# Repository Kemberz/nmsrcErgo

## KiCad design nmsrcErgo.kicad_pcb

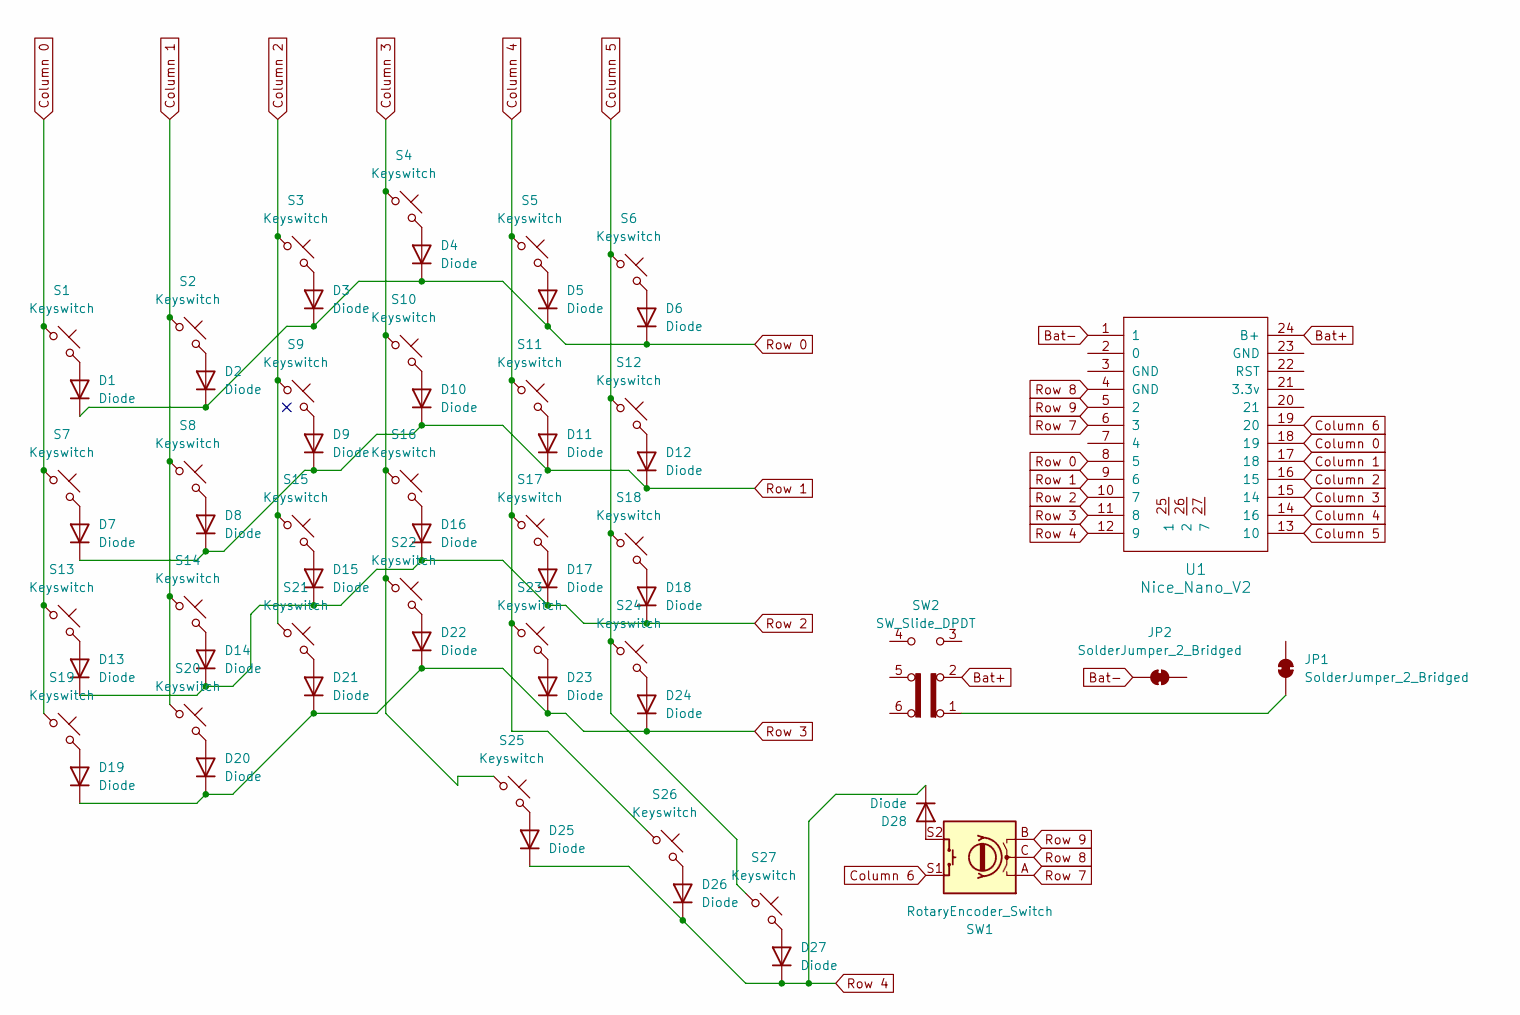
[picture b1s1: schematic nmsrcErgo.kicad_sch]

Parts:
D1, D2, D3, D4, D5, D6, D7, D8, D9, D10, D11, D12, D13, D14, D15, D16, D17, D18, D19, D20, D21, D22, D23, D24, D25, D26, D27, D28: Diode; Diode_DO-35
JP1, JP2: SolderJumper_2_Bridged; solderpadv2
S1, S2, S3, S4, S5, S6, S7, S8, S9, S10, S11, S12, S13, S14, S15, S16, S17, S18, S19, S20, S21, S22, S23, S24, S25, S26, S27: Keyswitch; Hotswap_Choc_V1
SW1: RotaryEncoder_Switch; Encoder_EC11_MX
SW2: SW_Slide_DPDT; SW_Slide-03_Wuerth-WS-SLTV_10x2.5x6.4_P2.54mm
U1: Nice_Nano_V2

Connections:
Bat+: SW2.2 (B), U1.24 (B+)
Bat-: JP2.1 (A), U1.1; also elsewhere on the board
Column 0: S1.1, S7.1, S13.1, S19.1, U1.18 (19)
Column 1: S2.1, S8.1, S14.1, S20.1, U1.17 (18)
Column 2: S3.1, S9.1, S15.1, S21.1, U1.16 (15)
Column 3: S4.1, S10.1, S16.1, S22.1, S25.1, U1.15 (14)
Column 4: S5.1, S11.1, S17.1, S23.1, S26.1, U1.14 (16)
Column 5: S6.1, S12.1, S18.1, S24.1, S27.1, U1.13 (10)
Column 6: SW1.S1, U1.19 (20)
unnamed: D1.2 (A), S1.2
unnamed: D2.2 (A), S2.2
unnamed: D3.2 (A), S3.2
unnamed: D4.2 (A), S4.2
unnamed: D5.2 (A), S5.2
unnamed: D6.2 (A), S6.2
unnamed: D7.2 (A), S7.2
unnamed: D8.2 (A), S8.2
unnamed: D9.2 (A), S9.2
unnamed: D10.2 (A), S10.2
unnamed: D11.2 (A), S11.2
unnamed: D12.2 (A), S12.2
unnamed: D13.2 (A), S13.2
unnamed: D14.2 (A), S14.2
unnamed: D15.2 (A), S15.2
unnamed: D16.2 (A), S16.2
unnamed: D17.2 (A), S17.2
unnamed: D18.2 (A), S18.2
unnamed: D19.2 (A), S19.2
unnamed: D20.2 (A), S20.2
unnamed: D21.2 (A), S21.2
unnamed: D22.2 (A), S22.2
unnamed: D23.2 (A), S23.2
unnamed: D24.2 (A), S24.2
unnamed: D25.2 (A), S25.2
unnamed: D26.2 (A), S26.2
unnamed: D27.2 (A), S27.2
unnamed: D28.2 (A), SW1.S2
unnamed 37: JP1.1 (A), SW2.1 (A); also elsewhere on the board
Row 0: D1.1 (K), D2.1 (K), D3.1 (K), D4.1 (K), D5.1 (K), D6.1 (K), U1.8 (5)
Row 1: D7.1 (K), D8.1 (K), D9.1 (K), D10.1 (K), D11.1 (K), D12.1 (K), U1.9 (6)
Row 2: D13.1 (K), D14.1 (K), D15.1 (K), D16.1 (K), D17.1 (K), D18.1 (K), U1.10 (7)
Row 3: D19.1 (K), D20.1 (K), D21.1 (K), D22.1 (K), D23.1 (K), D24.1 (K), U1.11 (8)
Row 4: D25.1 (K), D26.1 (K), D27.1 (K), D28.1 (K), U1.12 (9)
Row 7: SW1.A, U1.6 (3)
Row 8: SW1.C, U1.4 (GND)
Row 9: SW1.B, U1.5 (2)

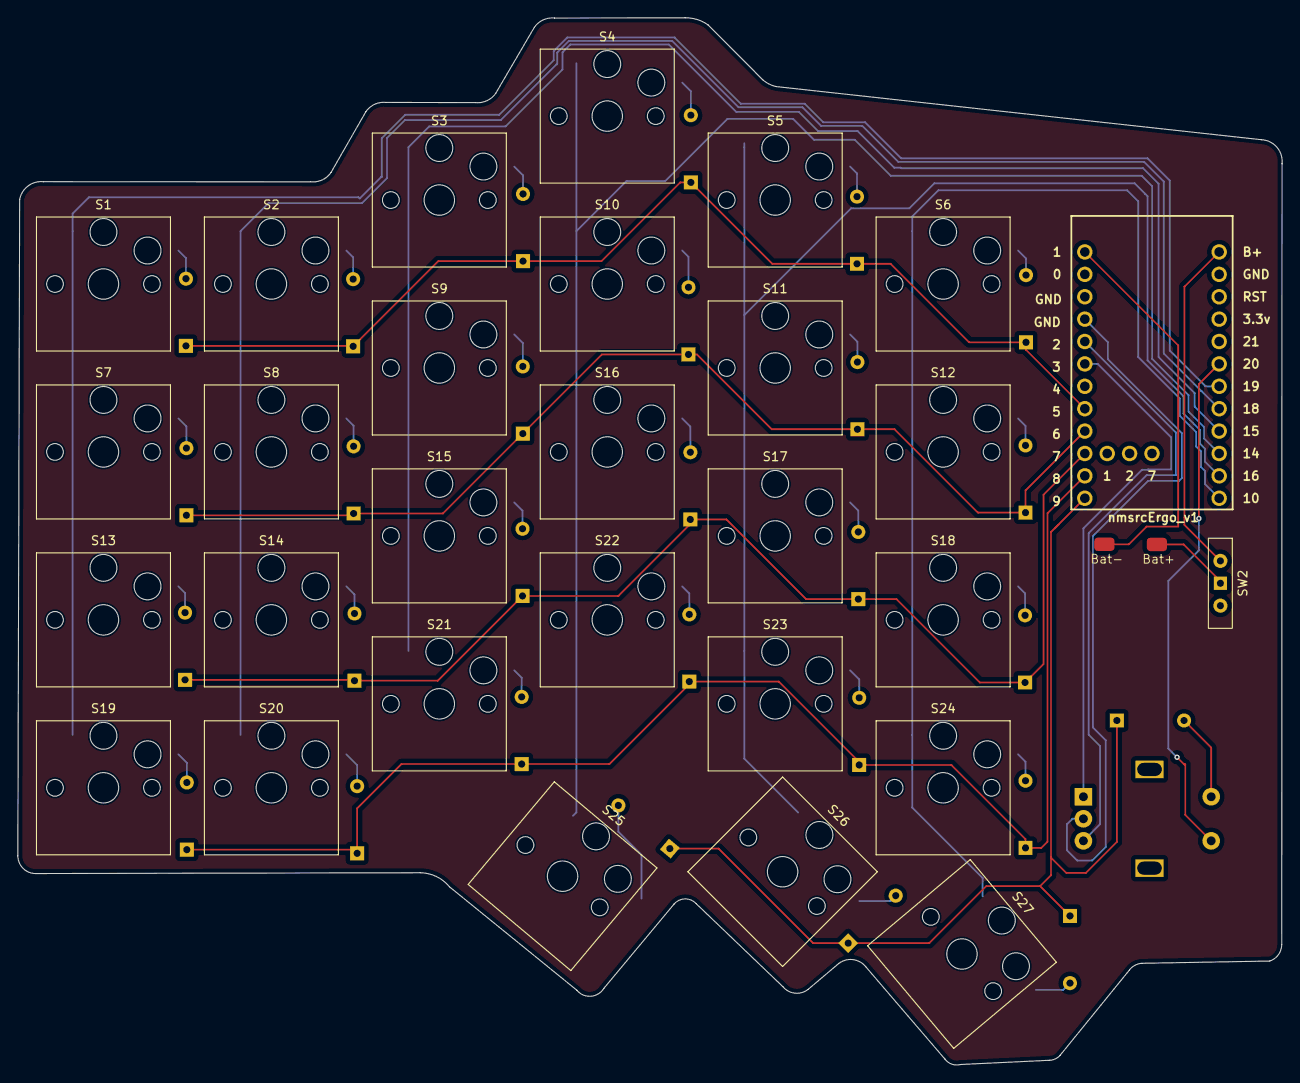
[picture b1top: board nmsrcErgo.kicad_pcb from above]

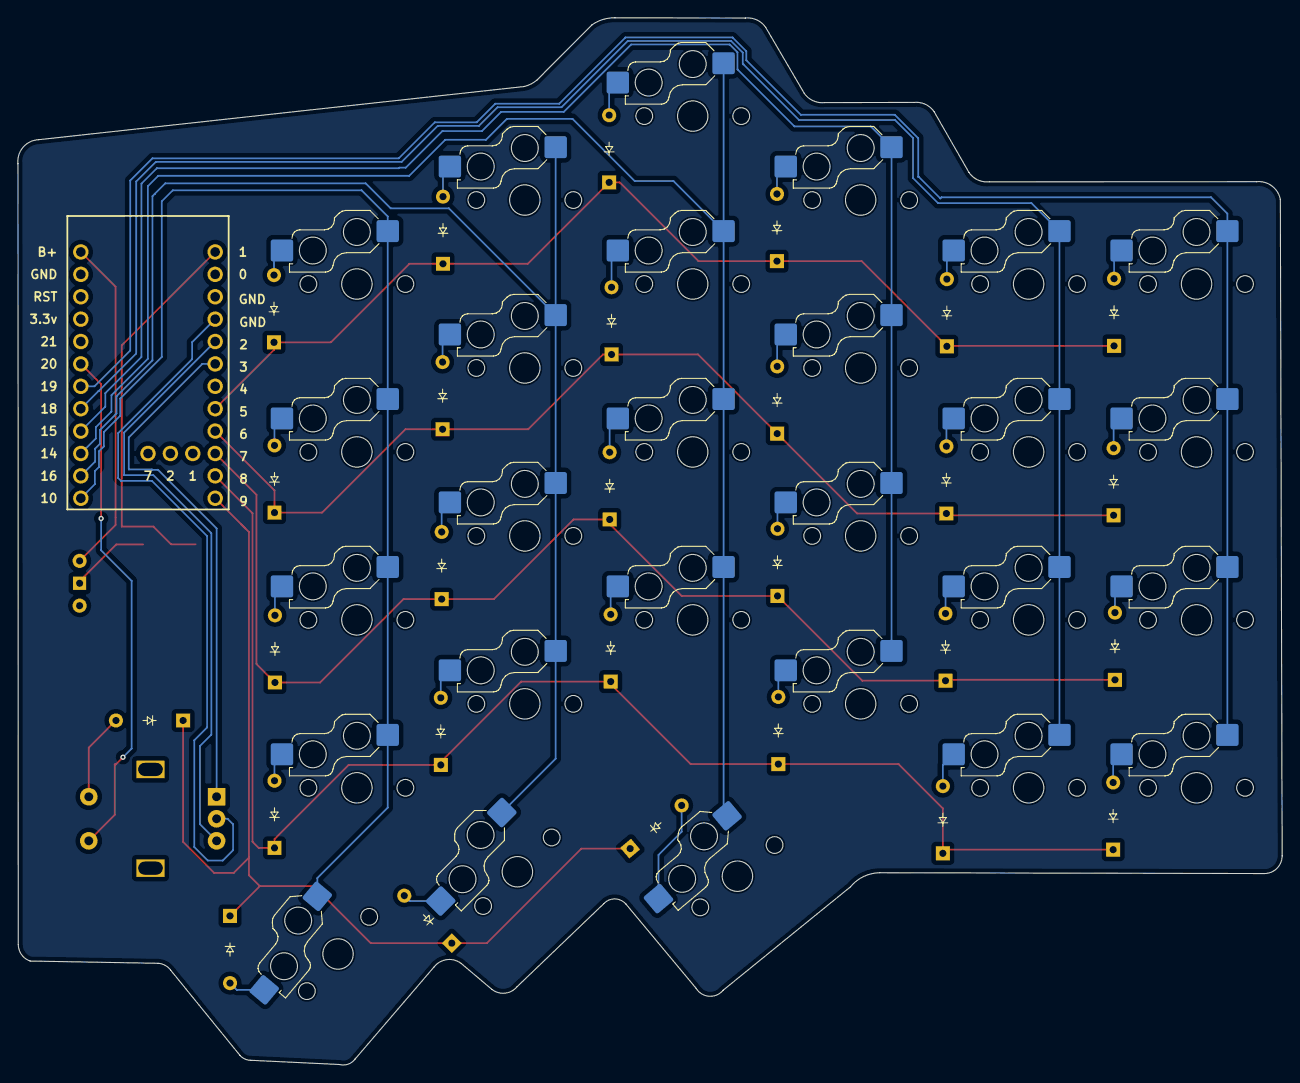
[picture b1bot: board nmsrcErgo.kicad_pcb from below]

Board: 2 copper layers, 143.4 x 118.8 mm, 60 parts (28 on the bottom side), 46 nets.

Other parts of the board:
Bat+: SolderJumper_2_Bridged; solderpadv2
Bat-: SolderJumper_2_Bridged; solderpadv2

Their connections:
Bat-: Bat-.1 (A); also elsewhere on the board
unnamed 37: Bat+.1 (A); also elsewhere on the board

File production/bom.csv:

Designator,Footprint,Quantity,Value,LCSC Part #
"D1, D10, D11, D12, D13, D14, D15, D16, D17, D18, D19, D2, D20, D21, D22, D23, D24, D25, D26, D27, D28, D3, D4, D5, D6, D7, D8, D9",Diode_DO-35,28,Diode,
"S1, S10, S11, S12, S13, S14, S15, S16, S17, S18, S19, S2, S20, S21, S22, S23, S24, S25, S26, S27, S3, S4, S5, S6, S7, S8, S9",Hotswap_Choc_V1,27,Keyswitch,
SW1,Encoder_EC11_MX,1,RotaryEncoder_Switch,
SW2,SW_Slide-03_Wuerth-WS-SLTV_10x2.5x6.4_P2.54mm,1,SW_Slide_DPDT,
U1,Nice_Nano_V2,1,Nice_Nano_V2,

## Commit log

2024-12-11 changed some keys orientation
2024-12-22 on/off switch and fixed encoder. added battery solder pads
